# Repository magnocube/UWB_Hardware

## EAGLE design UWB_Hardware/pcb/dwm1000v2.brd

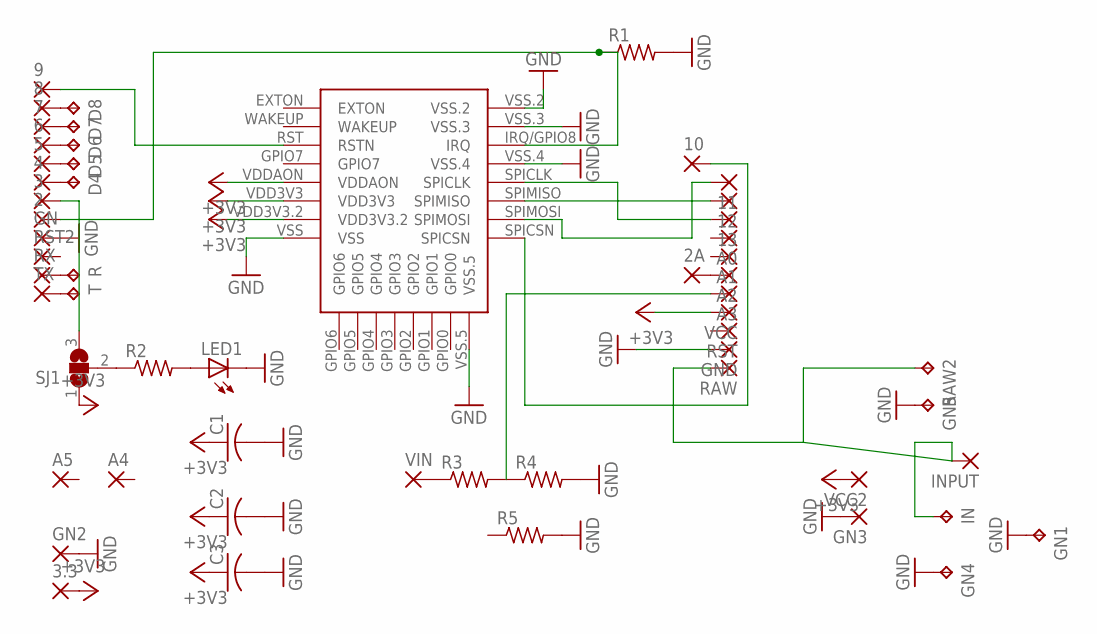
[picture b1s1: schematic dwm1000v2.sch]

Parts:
2, 2A, 3, 3.3, 4, 5, 6, 7, 8, 9, 10, 11, 12, 13: SMD2; SMD1,27-2,54
A0, A1, A2, A3: SMD2; SMD1,27-2,54
A4, A5: 1,6/0,8
C1, C2, C3: C-USC0805; C0805
D4, D5, D6, D7, D8: TPTP12SQ; TP12SQ
GN, GN2, GN3: SMD2; SMD1,27-2,54
GN1, GN4, GN5: TPTP13SQ; TP13SQ
GND: SMD2; SMD1,27-2,54
IN: TPTP13SQ; TP13SQ
INPUT: SMD2; SMD1,27-2,54
LED1: LEDCHIPLED_0805; CHIPLED_0805
R: TPTP12SQ; TP12SQ
R1: R-US_R0603; R0603
R2: R-US_M0805; M0805
R3, R4, R5: R-US_R0805; R0805
RAW: SMD2; SMD1,27-2,54
RAW2: TPTP13SQ; TP13SQ
RST, RST2: SMD2; SMD1,27-2,54
RX: SMD2; SMD1,27-2,54
SJ1: SJ2W; SJ_2
T: TPTP12SQ; TP12SQ
TX: SMD2; SMD1,27-2,54
U$1: DWM1000
VCC, VCC2: SMD2; SMD1,27-2,54
VIN: SMD2; SMD1,27-2,54

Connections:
+3V3: 3.3.1, C1.1, C2.1, C3.1, SJ1.1, U$1.VDD3V3, U$1.VDD3V3.2, U$1.VDDAON, VCC.1, VCC2.1
GND: C1.2, C2.2, C3.2, GN.1, GN1.TP, GN2.1, GN3.1, GN4.TP, GN5.TP, GND.1, LED1.C, R1.2, R4.2, R5.2, U$1.VSS, U$1.VSS.2, U$1.VSS.3, U$1.VSS.4, U$1.VSS.5
unnamed: 10.1, U$1.SPICSN
unnamed: 9.1, U$1.RST (RSTN)
unnamed: 12.1, U$1.SPIMISO
unnamed: 11.1, U$1.SPIMOSI
unnamed: 13.1, U$1.SPICLK
unnamed: 2.1, R1.1, U$1.IRQ/GPIO8 (IRQ)
unnamed: LED1.A, R2.2
unnamed: R2.1, SJ1.2
unnamed: 3.1, SJ1.3
unnamed: IN.TP, INPUT.1, RAW.1, RAW2.TP
unnamed: A3.1, R3.2, R4.1
unnamed: R3.1, VIN.1
unnamed: 2A.1, A2.1
unnamed: 7.1, D7.TP
unnamed: 6.1, D6.TP
unnamed: 5.1, D5.TP
unnamed: 4.1, D4.TP
unnamed: R.TP, RX.1
unnamed: T.TP, TX.1
unnamed: 8.1, D8.TP

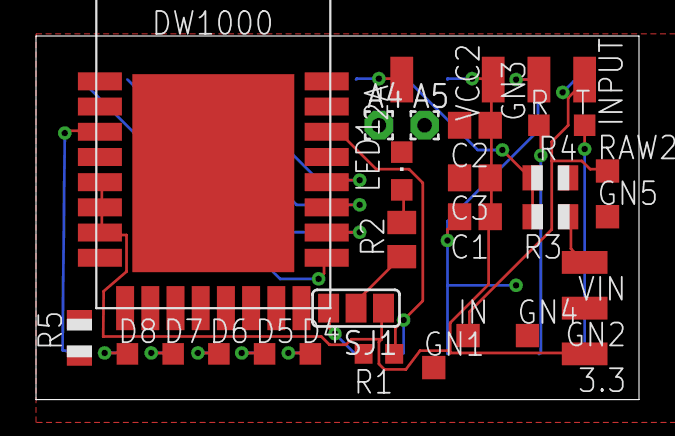
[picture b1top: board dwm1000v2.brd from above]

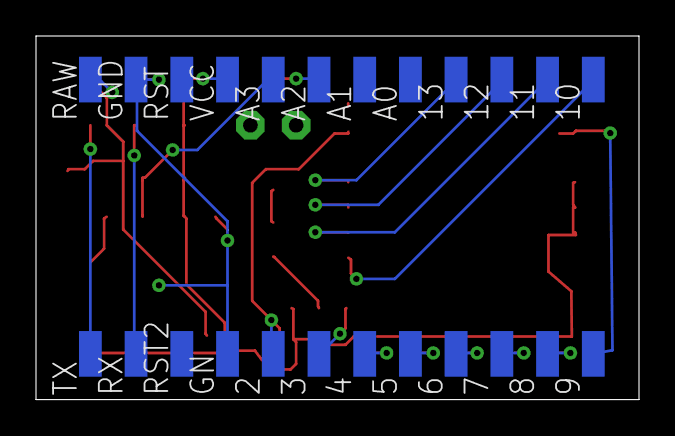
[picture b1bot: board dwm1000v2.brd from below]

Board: 2 copper layers, 33.5 x 20.2 mm, 56 parts (24 on the bottom side), 22 nets.

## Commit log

2017-11-25 hardware
2017-12-14 pcb's
2017-12-14 pcb documentatie bijgevoegd
2017-12-15 configurator added
2018-01-12 nieuwe uwb code, bijgewerkt configurator
2018-01-12 uwb update en nettere configurator
2018-01-17 final
2018-01-23 laatste update
